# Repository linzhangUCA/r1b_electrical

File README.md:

# r1b_electrical

## Schematic

## Assembled Example

## Errata

## Parts List

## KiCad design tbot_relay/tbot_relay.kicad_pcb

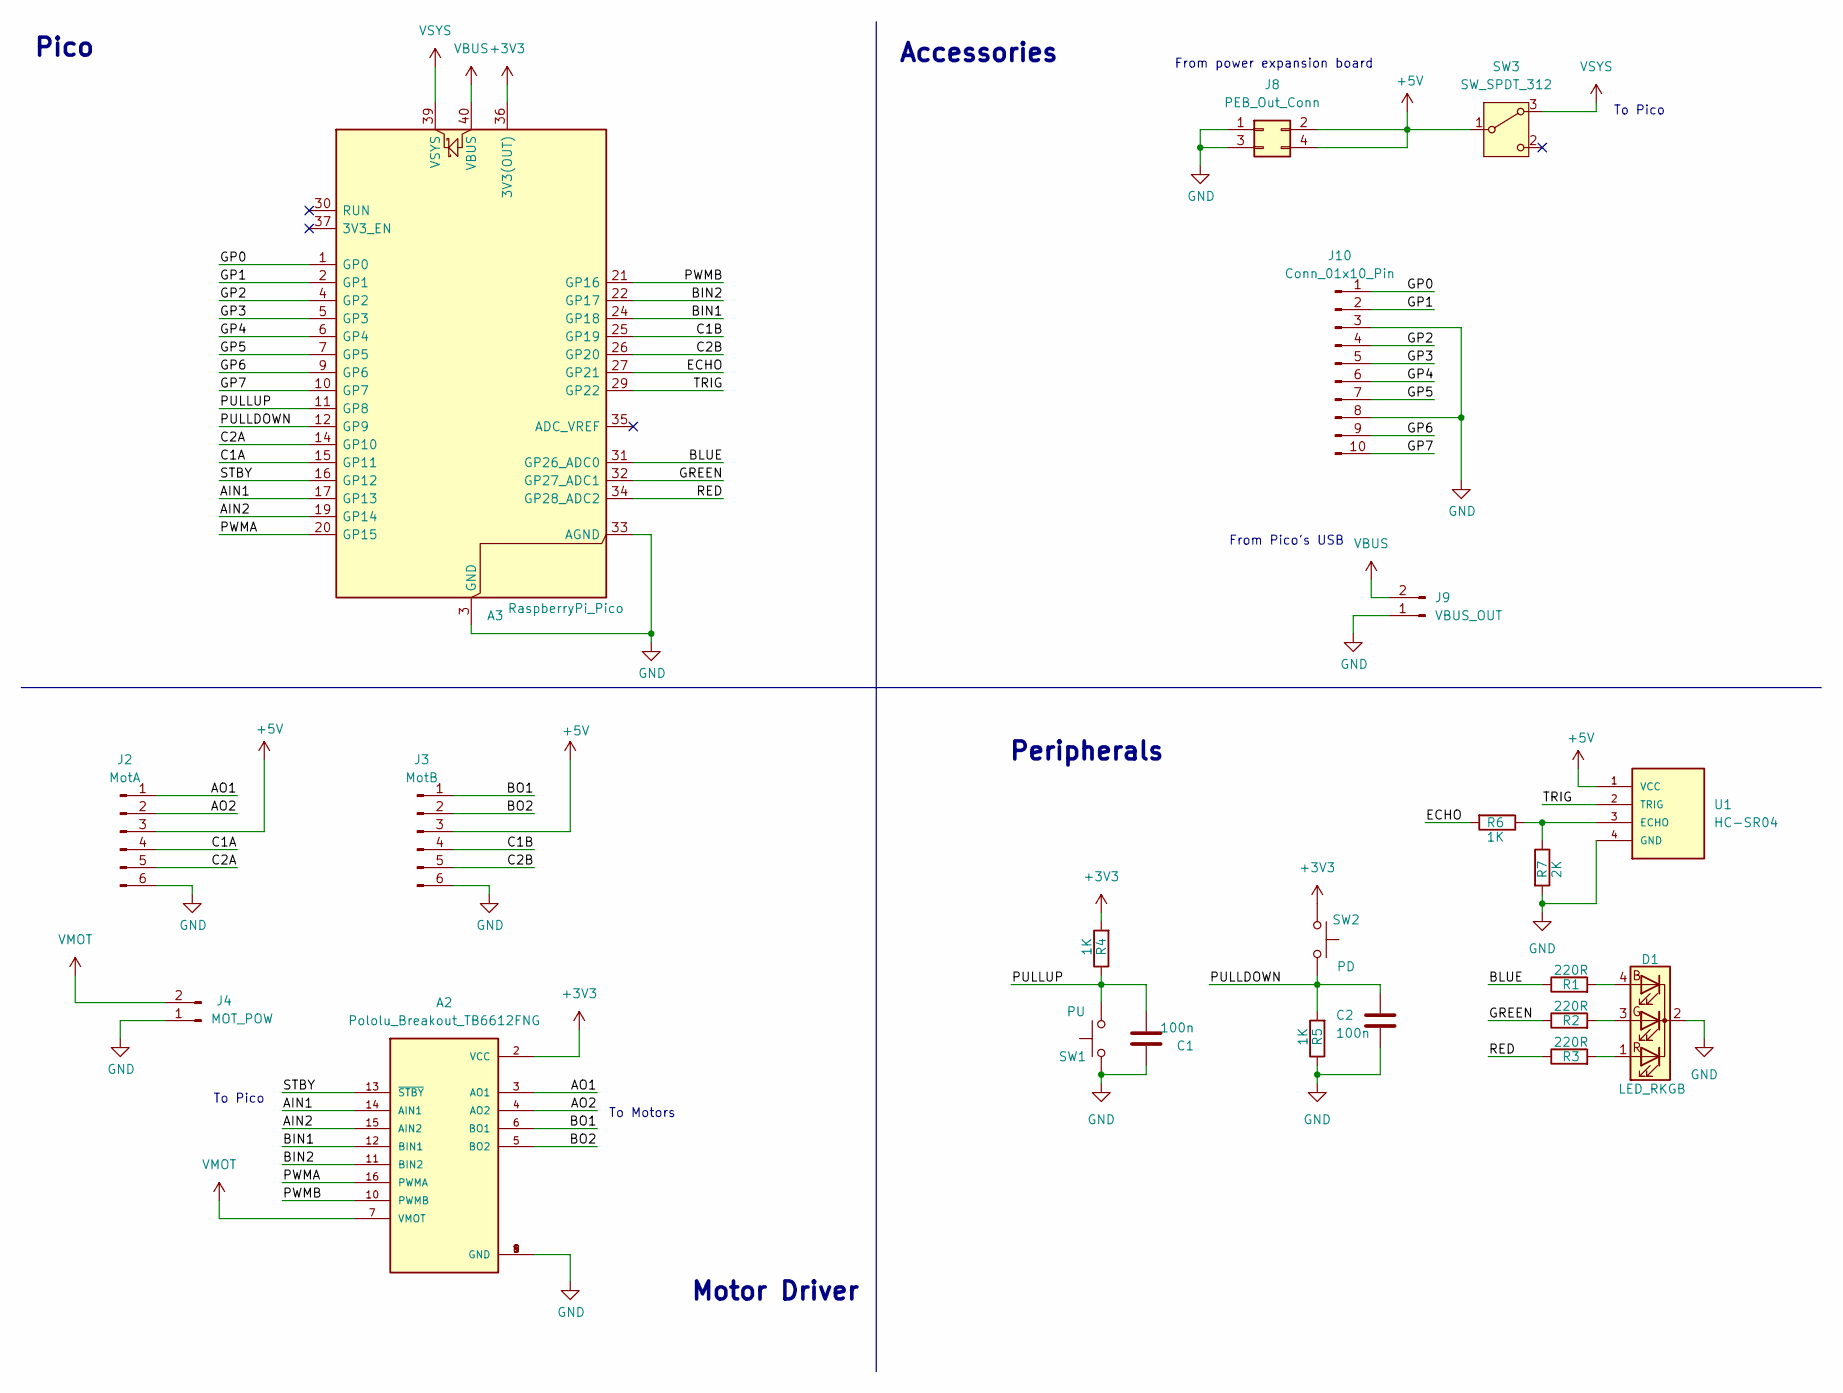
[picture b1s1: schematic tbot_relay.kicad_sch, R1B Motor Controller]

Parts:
A2: Pololu_Breakout_TB6612FNG; SHIELD_POLOLU-713
A3: RaspberryPi_Pico; RaspberryPi_Pico_Common_Unspecified
C1, C2: 100n; C_Disc_D4.7mm_W2.5mm_P5.00mm
D1: LED_RKGB; LED_D5.0mm-4_RGB_Wide_Pins
J2: MotA; PinHeader_1x06_P2.54mm_Vertical
J3: MotB; PinHeader_1x06_P2.54mm_Vertical
J4: MOT_POW; JST_XH_B2B-XH-A_1x02_P2.50mm_Vertical
J8: PEB_Out_Conn; PinHeader_2x02_P2.54mm_Vertical
J9: VBUS_OUT; PinHeader_1x02_P2.54mm_Vertical
J10: Conn_01x10_Pin; PinHeader_1x10_P2.54mm_Vertical
R1, R2, R3: 220R; R_Axial_DIN0207_L6.3mm_D2.5mm_P7.62mm_Horizontal
R4, R5, R6: 1K; R_Axial_DIN0207_L6.3mm_D2.5mm_P7.62mm_Horizontal
R7: 2K; R_Axial_DIN0207_L6.3mm_D2.5mm_P7.62mm_Horizontal
SW1: PU; SW_PUSH_6mm
SW2: PD; SW_PUSH_6mm
SW3: SW_SPDT_312; SW_Slide-03_Wuerth-WS-SLTV_10x2.5x6.4_P2.54mm
U1: HC-SR04; XCVR_HC-SR04

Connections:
+3V3: A2.2 (VCC), A3.36 (3V3(OUT)), R4.2, SW2.1
+5V: J2.3, J3.3, J8.2, J8.4, SW3.1 (B), U1.1 (VCC)
/AIN1: A2.14 (AIN1), A3.17 (GP13)
/AIN2: A2.15 (AIN2), A3.19 (GP14)
/AO1: A2.3 (AO1), J2.1
/AO2: A2.4 (AO2), J2.2
/BIN1: A2.12 (BIN1), A3.24 (GP18)
/BIN2: A2.11 (BIN2), A3.22 (GP17)
/BLUE: A3.31 (GP26_ADC0), R1.1
/BO1: A2.6 (BO1), J3.1
/BO2: A2.5 (BO2), J3.2
/C1A: A3.15 (GP11), J2.4
/C1B: A3.25 (GP19), J3.4
/C2A: A3.14 (GP10), J2.5
/C2B: A3.26 (GP20), J3.5
/ECHO: A3.27 (GP21), R6.2
/GP0: A3.1 (GP0), J10.1
/GP1: A3.2 (GP1), J10.2
/GP2: A3.4 (GP2), J10.4
/GP3: A3.5 (GP3), J10.5
/GP4: A3.6 (GP4), J10.6
/GP5: A3.7 (GP5), J10.7
/GP6: A3.9 (GP6), J10.9
/GP7: A3.10 (GP7), J10.10
/GREEN: A3.32 (GP27_ADC1), R2.1
/PULLDOWN: A3.12 (GP9), C2.2, R5.2, SW2.2
/PULLUP: A3.11 (GP8), C1.1, R4.1, SW1.2
/PWMA: A2.16 (PWMA), A3.20 (GP15)
/PWMB: A2.10 (PWMB), A3.21 (GP16)
/RED: A3.34 (GP28_ADC2), R3.1
/STBY: A2.13 (~STBY), A3.16 (GP12)
/TRIG: A3.29 (GP22), U1.2 (TRIG)
GND: A2.1 (GND), A2.8 (GND), A2.9 (GND), A3.3 (GND), A3.8 (GND), A3.13 (GND), A3.18 (GND), A3.23 (GND), A3.28 (GND), A3.33 (AGND), A3.38 (GND), C1.2, C2.1, D1.2 (K), J2.6, J3.6, J4.1, J8.1, J8.3, J9.1, J10.3, J10.8, R5.1, R7.2, SW1.1, U1.4 (GND)
unnamed: D1.4 (BA), R1.2
unnamed: D1.3 (GA), R2.2
unnamed: D1.1 (RA), R3.2
unnamed: R6.1, R7.1, U1.3 (ECHO)
VBUS: A3.40 (VBUS), J9.2
VMOT: A2.7 (VMOT), J4.2
VSYS: A3.39 (VSYS), SW3.3 (A)

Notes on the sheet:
Pico
From power expansion board
From Pico's USB
To Motors
Peripherals
To Pico
Motor Driver
Accessories

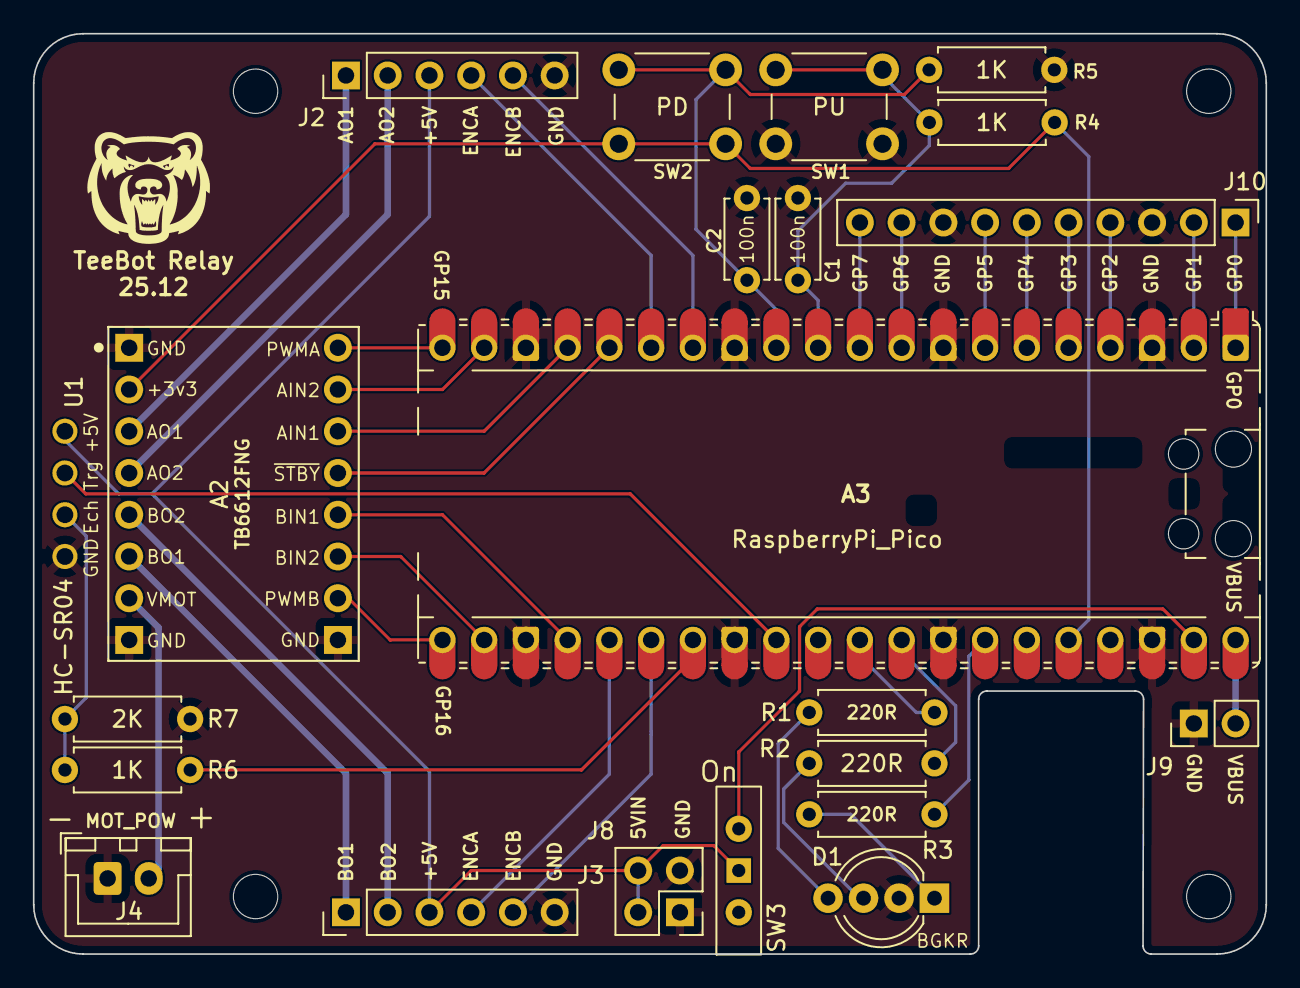
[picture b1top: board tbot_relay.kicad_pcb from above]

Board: 4 copper layers, 75.0 x 56.0 mm, 26 parts (0 on the bottom side), 40 nets.

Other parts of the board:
MH1, MH2, MH3, MH4: MountingHole_2.7mm_M2.5

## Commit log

2025-07-20 create KiCAD project
2025-07-20 add common cathod RGB LED to schematic
2025-07-20 add buttons and debounce circuits
2025-07-20 use net labels
2025-07-21 update schematic with ultrasound sensor
2025-07-21 add custom HC-SR04 symbol and footprint to project
2025-07-22 upload tb6612 breakout board library
2025-07-22 add motor driver and connectors
2025-07-24 replace switch with a jumper
2025-07-24 replace tb6612 power switch with a 01x02 pin header
2025-07-24 add comm connections between pi and pico
2025-07-29 finish up schematic
2025-07-31 assign footprints to capacitors
2025-07-31 assign footprints to resistors
2025-08-01 assign footprints to more parts
2025-08-01 assign all footprints
2025-08-13 update board setup and edge cuts
2025-08-13 update pico footprint
2025-08-13 layout v1
2025-08-14 wiring v1
2025-08-14 add 3d model for hcsr04
2025-08-14 update 3d model for hcsr04
2025-08-14 update tb6612 3d model
2025-08-14 update pico 3d model
2025-08-14 add bear head logo
2025-08-14 adjust labels
2025-08-16 final tweak pcb
2025-08-16 export gerber
2025-08-31 plot schematic
2025-09-06 fix hcsr04 voltage divider
2025-09-13 update schematic and pcb
    1. added a input 01x02 header for PEB power up +5V
    2. switched to +5V to power up sonar and encoders
    3. set jumper between +5V and PEB 5V input
    4. upgraded motor driver input to JST-XH
    5. updated footprints
2025-09-13 update schematic text labels
2025-10-23 update pull-down debouncer
2025-10-23 update REG_5V as source for all 5V components
2025-10-23 update unused GP pins net labels
2025-10-23 relabeling motor control wires
2025-10-24 rearange gp pins
2025-10-24 rearrange gp0 to gp7 connections
2025-10-24 assign footprint to connectors
2025-10-24 fix j9 footprint and update pcb
2025-10-24 update motor connector pins
2025-10-24 update layout
2025-10-24 minor update layout
2025-10-24 update wiring
2025-10-24 fix drc issues
2025-10-25 generate jlcpcb gerber
2025-10-25 update schematic pdf
2025-10-26 export board step
2025-11-16 upload an example
2025-11-16 add schematic image
2025-11-16 reserve parts list
2025-11-24 fix motor driver labels
2025-11-24 add motor driver errata
2025-12-22 update r1b design to tbot
2025-12-22 remove old gerbers
2025-12-22 remove old design
2025-12-22 save final changes
